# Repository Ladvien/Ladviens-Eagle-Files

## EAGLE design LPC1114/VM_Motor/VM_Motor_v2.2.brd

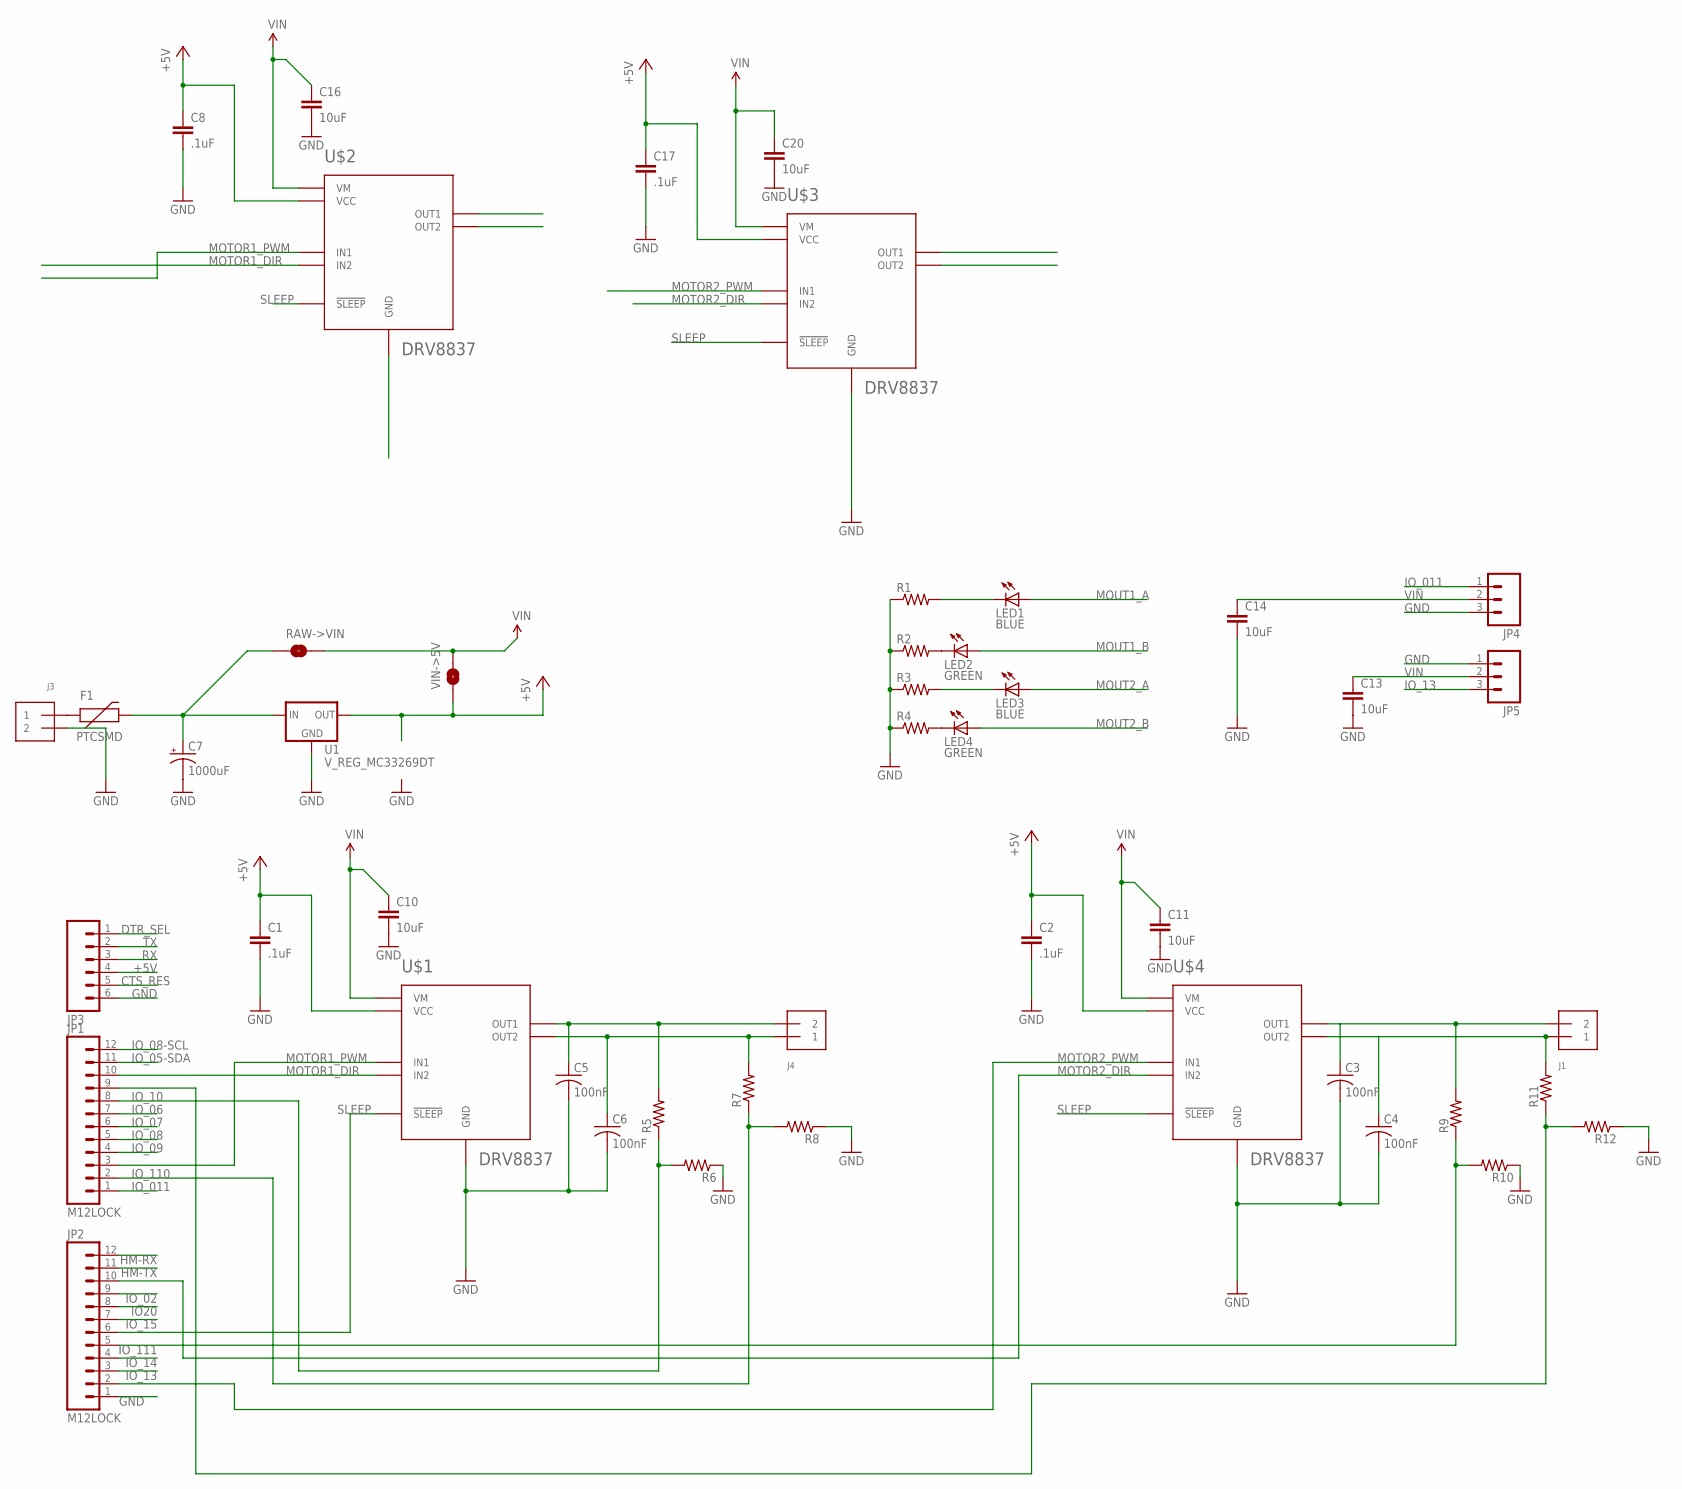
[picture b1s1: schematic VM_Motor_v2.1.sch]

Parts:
C1, C2, C8, C17: .1uF; 0402-CAP
C3, C4, C5, C6: 100nF; C0402
C7: 1000uF; 150CLZ-0810
C10, C11, C13, C14, C16, C20: 10uF; 0402-CAP
F1: PTCSMD; PTC-1206
J1, J3, J4: TERMBLOCK_1X2; TERMBLOCK_1X2-3.5MM
JP1, JP2: M12LOCK; 1X12_LOCK
JP3: M06LOCK; 1X06_LOCK
JP4, JP5: M03LOCK; 1X03_LOCK
LED1, LED3: BLUE; CHIP-LED0603
LED2, LED4: GREEN; CHIP-LED0603
R1, R2, R3, R4, R5, R6, R7, R8, R9, R10, R11, R12: R-US_R0402; R0402
RAW->VIN: SOLDERJUMPERNO; SJ_2S-NO
U1: V_REG_MC33269DT; DPAK
U$1, U$2, U$3, U$4: DRV8837; QFN8
VIN->5V: SOLDERJUMPERNO; SJ_2S-NO

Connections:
+5V: C1.1, C2.1, C8.1, C17.1, JP3.4, U1.4 (OUT), U$1.P$8 (VCC), U$2.P$8 (VCC), U$3.P$8 (VCC), U$4.P$8 (VCC), VIN->5V.1
CTS_RES: JP3.5
DTR_SEL: JP3.1
GND: C1.2, C2.2, C3.2, C4.2, C5.2, C6.2, C7.-, C8.2, C10.2, C11.2, C13.2, C14.2, C16.2, C17.2, C20.2, J3.2, JP2.1, JP3.6, JP4.3, JP5.1, R1.1, R2.1, R3.1, R4.1, R6.1, R8.1, R10.1, R12.1, U1.1 (GND), U$1.P$4 (GND), U$1.P$9 (GND), U$1.P$10 (GND), U$1.P$11 (GND), U$2.P$4 (GND), U$2.P$9 (GND), U$2.P$10 (GND), U$2.P$11 (GND), U$3.P$4 (GND), U$3.P$9 (GND), U$3.P$10 (GND), U$3.P$11 (GND), U$4.P$4 (GND), U$4.P$9 (GND), U$4.P$10 (GND), U$4.P$11 (GND)
HM-RX: JP2.12
HM-TX: JP2.11
IO20: JP2.8
IO_02: JP2.9
IO_05-SDA: JP1.11
IO_06: JP1.7
IO_07: JP1.6
IO_08: JP1.5
IO_08-SCL: JP1.12
IO_09: JP1.4
IO_10: JP1.8, R5.1, R6.2
IO_011: JP1.1, JP4.1
IO_11: JP1.9, R11.1, R12.2
IO_13: JP2.3, JP5.3
IO_14: JP2.4
IO_15: JP2.7
IO_110: JP1.2, R7.1, R8.2
IO_111: JP2.5, R9.1, R10.2
MOTOR1_DIR: JP1.10, U$1.P$5 (IN2), U$2.P$5 (IN2)
MOTOR1_PWM: JP1.3, U$1.P$6 (IN1), U$2.P$6 (IN1)
MOTOR2_DIR: JP2.10, U$3.P$5 (IN2), U$4.P$5 (IN2)
MOTOR2_PWM: JP2.2, U$3.P$6 (IN1), U$4.P$6 (IN1)
MOUT1_A: C5.1, J4.2, LED1.A, R5.2, U$1.P$2 (OUT1), U$2.P$2 (OUT1)
MOUT1_B: C6.1, J4.1, LED2.A, R7.2, U$1.P$3 (OUT2), U$2.P$3 (OUT2)
MOUT2_A: C3.1, J1.2, LED3.A, R9.2, U$3.P$2 (OUT1), U$4.P$2 (OUT1)
MOUT2_B: C4.1, J1.1, LED4.A, R11.2, U$3.P$3 (OUT2), U$4.P$3 (OUT2)
unnamed: LED2.C, R2.2
unnamed: LED4.C, R4.2
unnamed: LED1.C, R1.2
unnamed: LED3.C, R3.2
unnamed: F1.1, J3.1
RAW: C7.+, F1.2, RAW->VIN.1, U1.3 (IN)
RX: JP3.3
SLEEP: JP2.6, U$1.P$7 (!SLEEP), U$2.P$7 (!SLEEP), U$3.P$7 (!SLEEP), U$4.P$7 (!SLEEP)
TX: JP3.2
VIN: C10.1, C11.1, C13.1, C14.1, C16.1, C20.1, JP4.2, JP5.2, RAW->VIN.2, U$1.P$1 (VM), U$2.P$1 (VM), U$3.P$1 (VM), U$4.P$1 (VM), VIN->5V.2

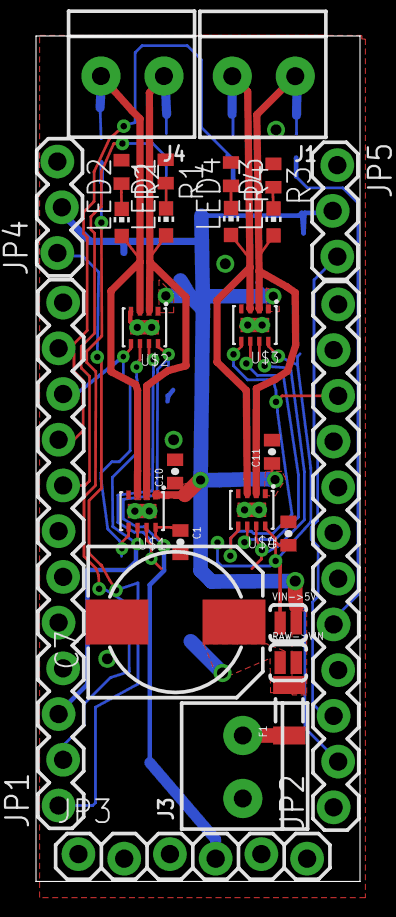
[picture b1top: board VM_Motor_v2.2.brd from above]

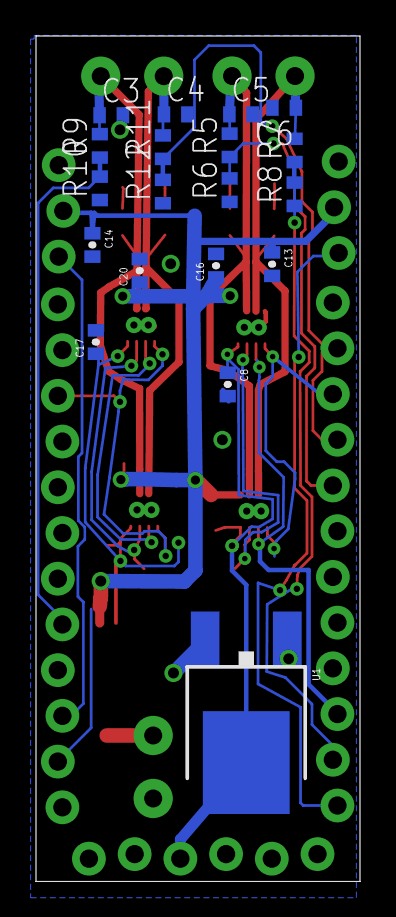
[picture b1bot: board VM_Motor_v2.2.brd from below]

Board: 2 copper layers, 18.0 x 47.0 mm, 47 parts (19 on the bottom side), 24 nets.

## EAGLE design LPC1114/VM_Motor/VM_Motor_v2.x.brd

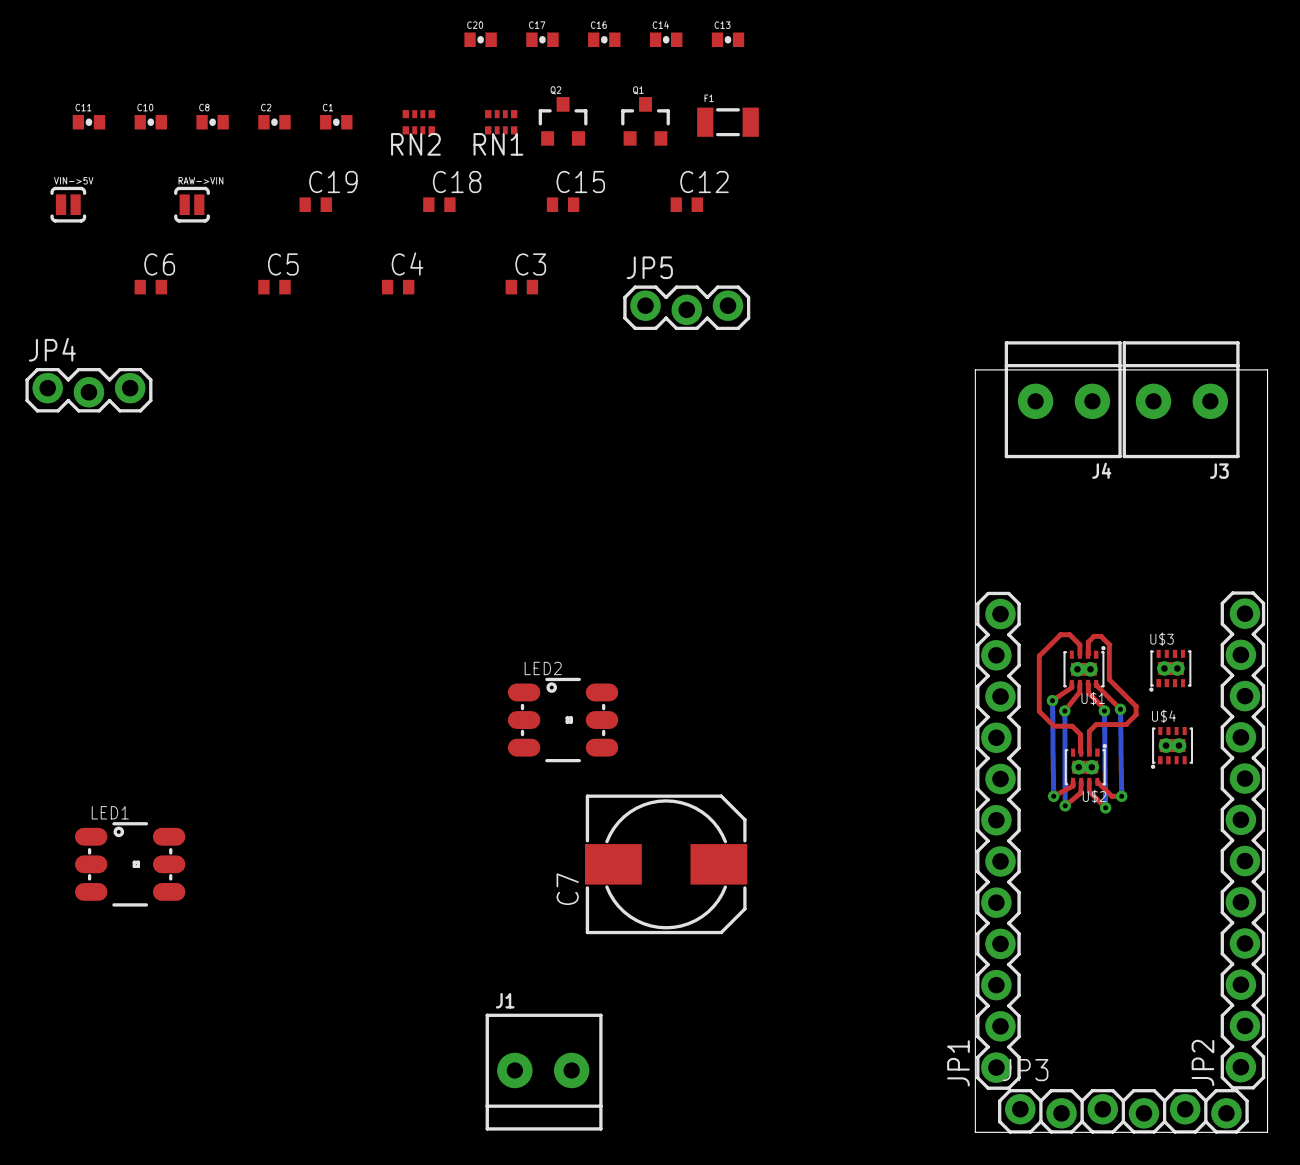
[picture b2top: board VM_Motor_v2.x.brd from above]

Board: 2 copper layers, 18.0 x 47.0 mm, 40 parts (0 on the bottom side), 28 nets.

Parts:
C1, C2, C8, C17: .1uF; 0402-CAP
C3, C4, C5, C6, C12, C15, C18, C19: 100nF; C0402
C7: 1000uF; 150CLZ-0810
C10, C11, C13, C14, C16, C20: 10uF; 0402-CAP
F1: PTCSMD; PTC-1206
J1, J3, J4: TERMBLOCK_1X2-3.5MM
JP1, JP2: M12LOCK; 1X12_LOCK
JP3: 1X06_LOCK
JP4, JP5: 1X03_LOCK
LED1, LED2: LED-TRICOLOR-5050NO_IC; LED-TRICOLOR-5050
Q1, Q2: MMBT2222A; SOT23-3
RAW->VIN: SOLDERJUMPERNO; SJ_2S-NO
RN1, RN2: 4X0402ARV341
U$1, U$2, U$3, U$4: DRV8837; QFN8
VIN->5V: SOLDERJUMPERNO; SJ_2S-NO

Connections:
+5V: C1.1, C2.1, C8.1, C17.1, JP3.4, U$1.P$8, U$2.P$8, U$3.P$8, U$4.P$8, VIN->5V.1
GND: C1.2, C2.2, C3.2, C4.2, C5.2, C6.2, C7.-, C8.2, C10.2, C11.2, C12.2, C13.2, C14.2, C15.2, C16.2, C17.2, C18.2, C19.2, C20.2, J3.2, JP2.1, JP3.6, JP4.3, JP5.1, Q1.2, Q2.2, RN1.1, RN1.4, RN2.1, RN2.4, U$1.P$4, U$1.P$9, U$1.P$10, U$1.P$11, U$2.P$4, U$2.P$9, U$2.P$10, U$2.P$11, U$3.P$4, U$3.P$9, U$3.P$10, U$3.P$11, U$4.P$4, U$4.P$9, U$4.P$10, U$4.P$11
IO20: JP2.8, RN2.3
IO_07: JP1.6, RN1.3
IO_011: JP1.1, JP4.1
IO_13: JP2.3, JP5.3
MOTOR1_DIR: JP1.10, U$1.P$5, U$2.P$5
MOTOR1_PWM: JP1.9, U$1.P$6, U$2.P$6
MOTOR2_DIR: JP2.10, U$3.P$5, U$4.P$5
MOTOR2_PWM: JP2.2, U$3.P$6, U$4.P$6
MOUT1_A: C5.1, C12.1, J4.2, LED1.3, U$1.P$2, U$2.P$2
MOUT1_B: C6.1, C15.1, J4.1, LED1.1, U$1.P$3, U$2.P$3
MOUT2_A: C3.1, C18.1, J1.2, LED2.3, U$3.P$2, U$4.P$2
MOUT2_B: C4.1, C19.1, J1.1, LED2.1, U$3.P$3, U$4.P$3
unnamed: Q1.1, RN2.6
unnamed: LED1.4, RN1.8
unnamed: LED1.6, RN1.5
unnamed: LED2.4, RN2.8
unnamed: LED1.5, RN1.7
unnamed: Q1.3, RN2.2
unnamed: Q2.3, RN1.2
unnamed: Q2.1, RN1.6
unnamed: LED2.6, RN2.5
unnamed: LED2.5, RN2.7
unnamed: F1.1, J3.1
RAW: C7.+, F1.2, RAW->VIN.1
SLEEP: JP2.6, U$1.P$7, U$2.P$7, U$3.P$7, U$4.P$7
VIN: C10.1, C11.1, C13.1, C14.1, C16.1, JP4.2, JP5.2, LED1.2, LED2.2, RAW->VIN.2, U$1.P$1, U$2.P$1, U$3.P$1, U$4.P$1, VIN->5V.2

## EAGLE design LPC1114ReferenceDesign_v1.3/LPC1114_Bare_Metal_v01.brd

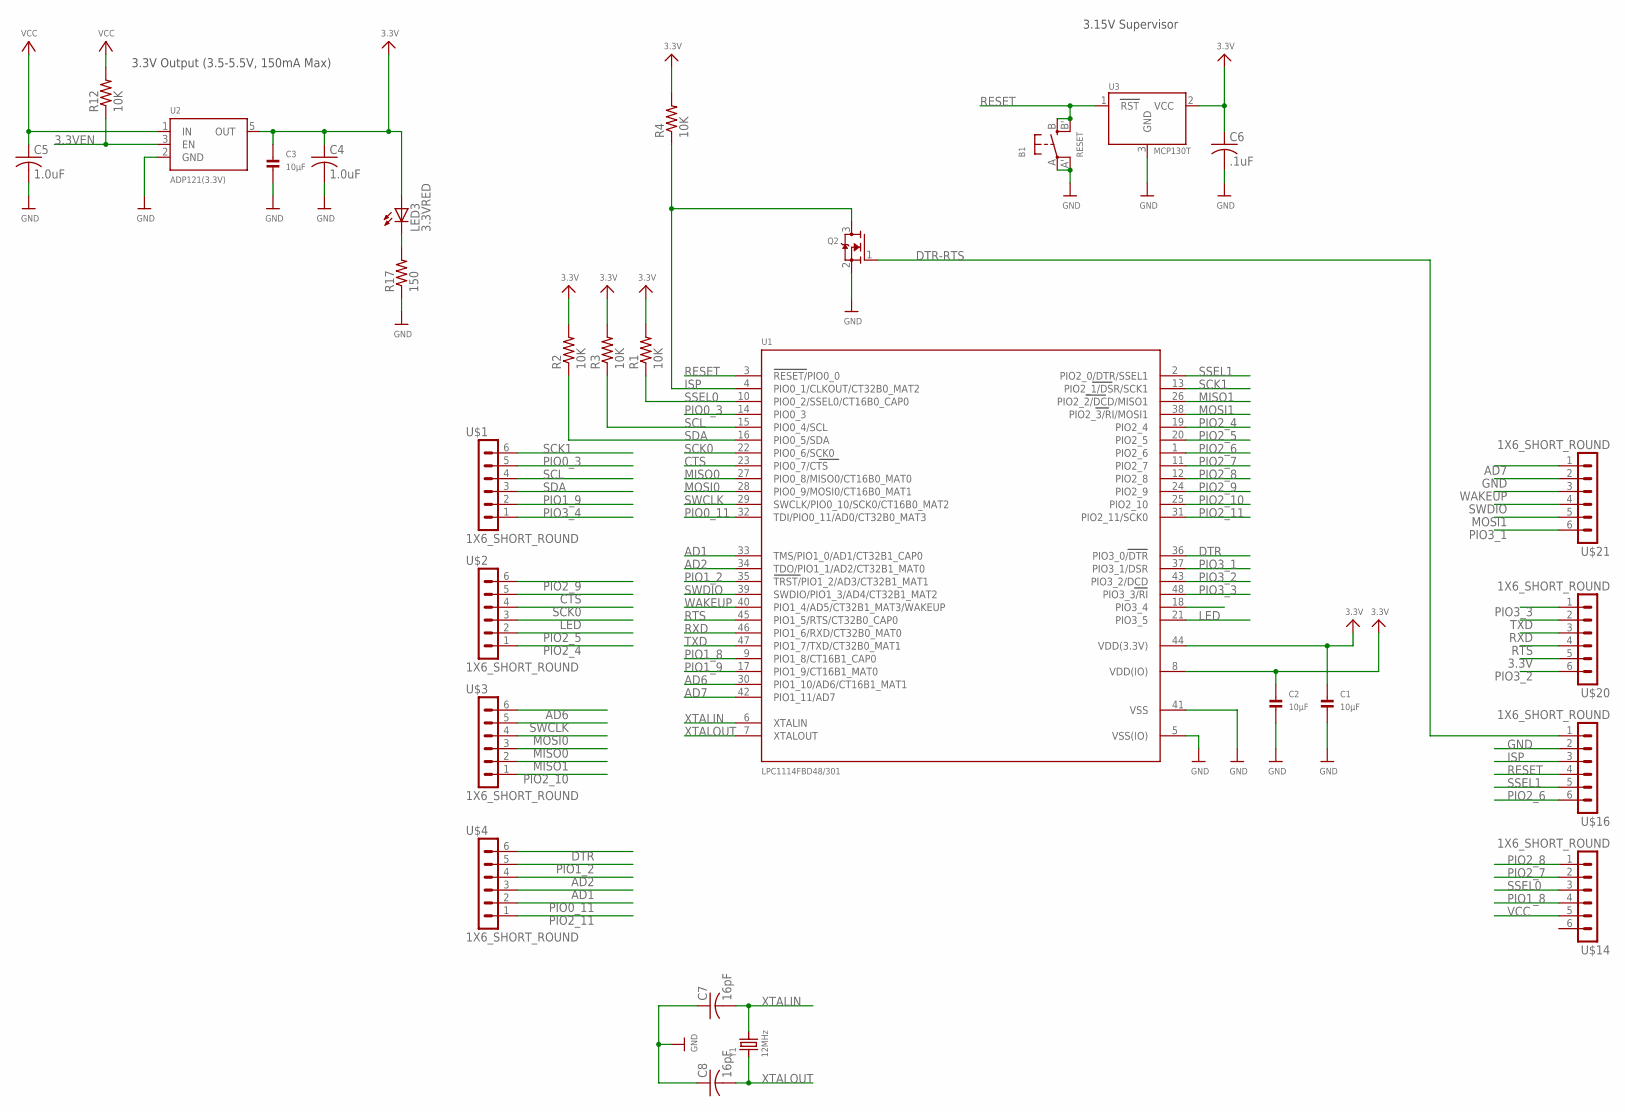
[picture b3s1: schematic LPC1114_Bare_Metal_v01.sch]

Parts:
B1: RESET; EVQ-Q2
C1, C2, C3: 10µF; 0805
C4, C5: 1.0uF; C0402K
C6: .1uF; C0402K
C7, C8: 16pF; C0402K
LED3: 3.3VRED; SML0603
Q2: MOSFET-NREFLOW; SOT23
R1, R2, R3, R4, R12: 10K; R0402
R17: 150; R0402
U1: LPC1114FBD48/301; LQFP48
U2: ADP121(3.3V); SOT23-5
U3: MCP130T; SOT23-R
U$1, U$2, U$3, U$4, U$14, U$16, U$20, U$21: 1X6_SHORT_ROUND
Y1: 12MHz; CRYSTAL_3.2X2.5

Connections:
3.3V: C1.1, C2.1, C3.1, C4.1, C6.1, LED3.A, R1.2, R2.2, R3.2, R4.2, U1.8 (VDD(IO)), U1.44 (VDD(3.3V)), U2.5 (OUT), U3.2 (VCC), U$20.5
3.3VEN: R12.1, U2.3 (EN)
AD1: U1.33 (TMS/PIO1_0/AD1/CT32B1_CAP0), U$4.3
AD2: U1.34 (TDO/PIO1_1/AD2/CT32B1_MAT0), U$4.4
AD6: U1.30 (PIO1_10/AD6/CT16B1_MAT1), U$3.6
AD7: U1.42 (PIO1_11/AD7), U$21.1
CTS: U1.23 (PIO0_7/CTS), U$2.5
DTR: U1.36 (PIO3_0/DTR), U$4.6
DTR-RTS: Q2.1 (G), U$16.1
GND: B1.A, B1.A' (P1), C1.2, C2.2, C3.2, C4.2, C5.2, C6.2, C7.1, C8.1, Q2.2 (S), R17.1, U1.5 (VSS(IO)), U1.41 (VSS), U2.2 (GND), U3.3 (GND), U$16.2, U$21.2
ISP: Q2.3 (D), R4.1, U1.4 (PIO0_1/CLKOUT/CT32B0_MAT2), U$16.3
LED: U1.21 (PIO3_5), U$2.3
MISO0: U1.27 (PIO0_8/MISO0/CT16B0_MAT0), U$3.3
MISO1: U1.26 (PIO2_2/DCD/MISO1), U$3.2
MOSI0: U1.28 (PIO0_9/MOSI0/CT16B0_MAT1), U$3.4
MOSI1: U1.38 (PIO2_3/RI/MOSI1), U$21.5
unnamed: LED3.C, R17.2
PIO0_3: U1.14 (PIO0_3), U$1.5
PIO0_11: U1.32 (TDI/PIO0_11/AD0/CT32B0_MAT3), U$4.2
PIO1_2: U1.35 (TRST/PIO1_2/AD3/CT32B1_MAT1), U$4.5
PIO1_8: U1.9 (PIO1_8/CT16B1_CAP0), U$14.4
PIO1_9: U1.17 (PIO1_9/CT16B1_MAT0), U$1.2
PIO2_4: U1.19 (PIO2_4), U$2.1
PIO2_5: U1.20 (PIO2_5), U$2.2
PIO2_6: U1.1 (PIO2_6), U$16.6
PIO2_7: U1.11 (PIO2_7), U$14.2
PIO2_8: U1.12 (PIO2_8), U$14.1
PIO2_9: U1.24 (PIO2_9), U$2.6
PIO2_10: U1.25 (PIO2_10), U$3.1
PIO2_11: U1.31 (PIO2_11/SCK0), U$4.1
PIO3_1: U1.37 (PIO3_1/DSR), U$21.6
PIO3_2: U1.43 (PIO3_2/DCD), U$20.6
PIO3_3: U1.48 (PIO3_3/RI), U$20.1
PIO3_4: U1.18 (PIO3_4), U$1.1
RESET: B1.B (S), B1.B' (S1), U1.3 (RESET/PIO0_0), U3.1 (RST), U$16.4
RTS: U1.45 (PIO1_5/RTS/CT32B0_CAP0), U$20.4
RXD: U1.46 (PIO1_6/RXD/CT32B0_MAT0), U$20.3
SCK0: U1.22 (PIO0_6/SCK0), U$2.4
SCK1: U1.13 (PIO2_1/DSR/SCK1), U$1.6
SCL: R3.1, U1.15 (PIO0_4/SCL), U$1.4
SDA: R2.1, U1.16 (PIO0_5/SDA), U$1.3
SSEL0: R1.1, U1.10 (PIO0_2/SSEL0/CT16B0_CAP0), U$14.3
SSEL1: U1.2 (PIO2_0/DTR/SSEL1), U$16.5
SWCLK: U1.29 (SWCLK/PIO0_10/SCK0/CT16B0_MAT2), U$3.5
SWDIO: U1.39 (SWDIO/PIO1_3/AD4/CT32B1_MAT2), U$21.4
TXD: U1.47 (PIO1_7/TXD/CT32B0_MAT1), U$20.2
VCC: C5.1, R12.2, U2.1 (IN), U$14.5
WAKEUP: U1.40 (PIO1_4/AD5/CT32B1_MAT3/WAKEUP), U$21.3
XTALIN: C7.2, U1.6 (XTALIN), Y1.2
XTALOUT: C8.2, U1.7 (XTALOUT), Y1.1

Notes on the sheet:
3.3V Output (3.5-5.5V, 150mA Max)
3.15V Supervisor

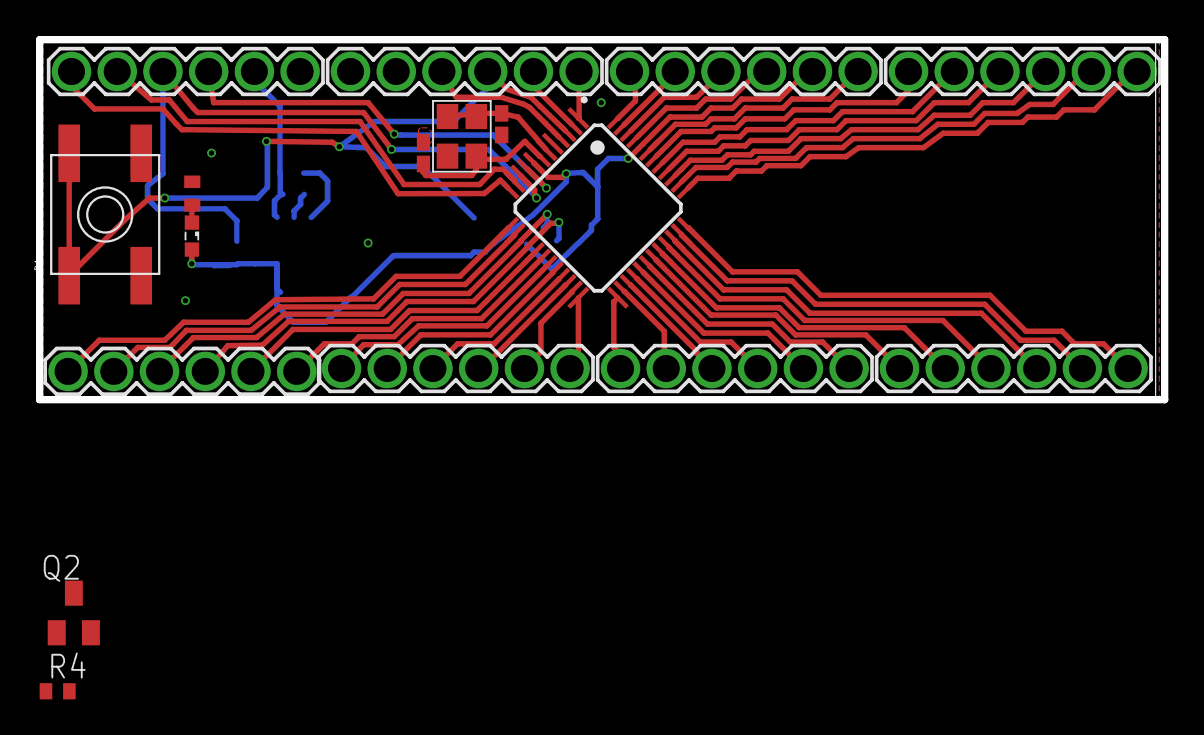
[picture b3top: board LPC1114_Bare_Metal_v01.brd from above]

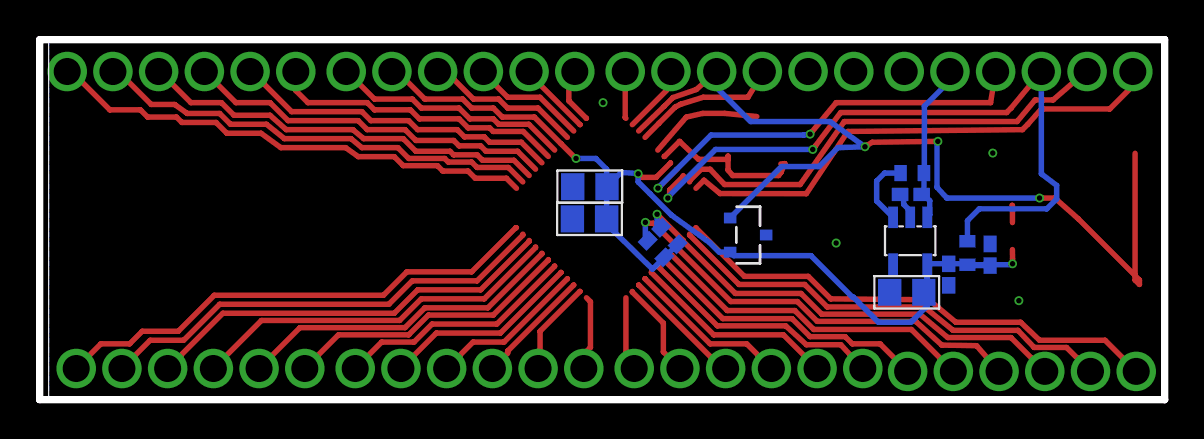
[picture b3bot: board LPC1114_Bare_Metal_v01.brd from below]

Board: 2 copper layers, 62.5 x 20.0 mm, 29 parts (12 on the bottom side), 50 nets.

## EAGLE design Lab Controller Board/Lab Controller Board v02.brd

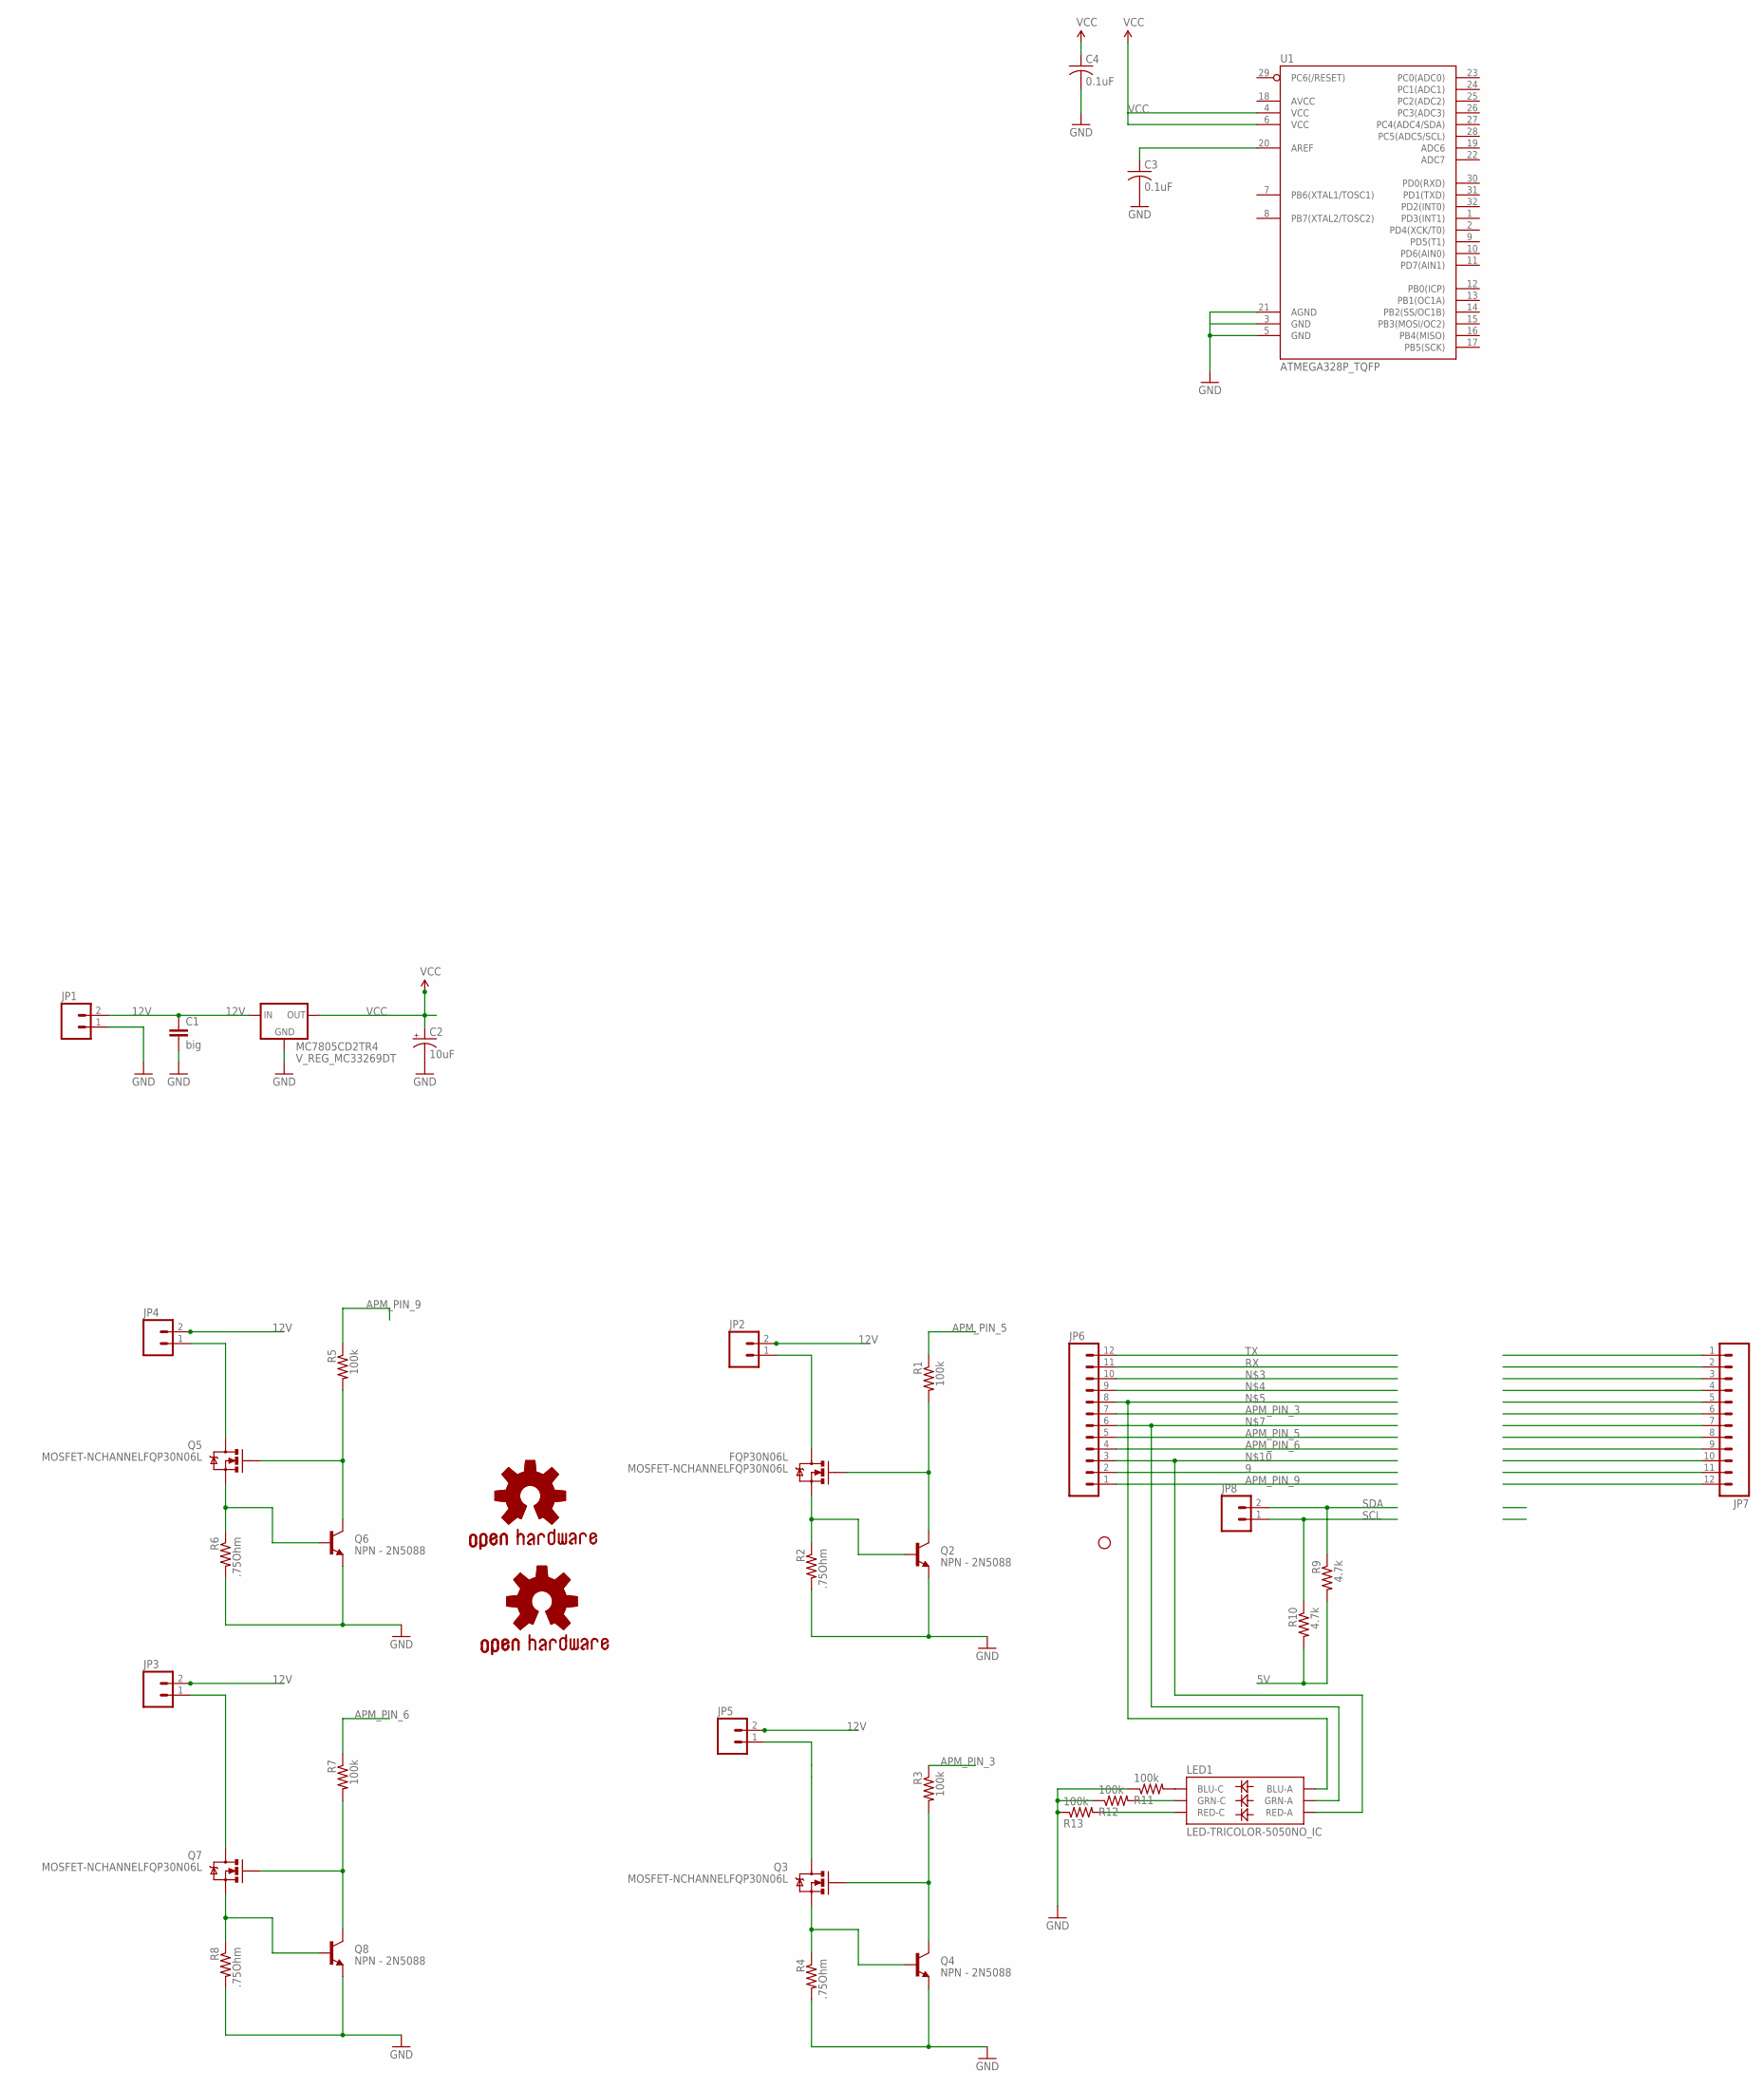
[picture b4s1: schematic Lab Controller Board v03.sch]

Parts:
C1: big; CAP-PTH-5MM
C2: 10uF; EIA3528
C3, C4: 0.1uF; C0402
FQP30N06L: MOSFET-NCHANNELFQP30N06L; TO220V
GOLD_ORB_SM1: OSHWLOGO_GOLD_ORB_MED; OSHW1
GOLD_ORB_SM2: OSHWLOGO_GOLD_ORB_SM; OSHW2
JP1, JP2, JP3, JP4, JP5: M025MM; SCREWTERMINAL-5MM-2
JP6, JP7: M12PTH; 1X12
JP8: M02LOCK; 1X02_LOCK
LED1: LED-TRICOLOR-5050NO_IC; LED-TRICOLOR-5050
MC7805CD2TR4: V_REG_MC33269DT; DPAK
Q2, Q4, Q6, Q8: NPN - 2N5088; TO-92
Q3, Q5, Q7: MOSFET-NCHANNELFQP30N06L; TO220V
R1, R3, R5, R7, R11, R12, R13: 100k; R0805W
R2, R4, R6, R8: .75Ohm; 0411V
R9, R10: 4.7k; M0805
STANDOFF1: STAND-OFF
U1: ATMEGA328P_TQFP; TQFP32-08

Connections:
12V: C1.1, JP1.2, JP2.2, JP3.2, JP4.2, JP5.2, MC7805CD2TR4.3 (IN)
APM_PIN_3: JP6.7, R3.1; also elsewhere on the board
APM_PIN_5: JP6.5, R1.1; also elsewhere on the board
APM_PIN_6: JP6.4, R7.1; also elsewhere on the board
APM_PIN_9: JP6.1, R5.1; also elsewhere on the board
FET_SOURCE: FQP30N06L.3 (S), Q2.2 (B), R2.1
FET_SOURCE1: Q3.3 (S), Q4.2 (B), R4.1
FET_SOURCE2: Q5.3 (S), Q6.2 (B), R6.1
FET_SOURCE3: Q7.3 (S), Q8.2 (B), R8.1
GND: C1.2, C2.C (-), C3.2, C4.2, JP1.1, MC7805CD2TR4.1 (GND), Q2.1 (E), Q4.1 (E), Q6.1 (E), Q8.1 (E), R2.2, R4.2, R6.2, R8.2, R11.1, R12.1, R13.1, U1.3 (GND), U1.5 (GND), U1.21 (AGND); also elsewhere on the board
LED_DRAIN: FQP30N06L.2 (D), JP2.1
LED_DRAIN1: JP5.1, Q3.2 (D)
LED_DRAIN2: JP4.1, Q5.2 (D)
LED_DRAIN3: JP3.1, Q7.2 (D)
unnamed 14: JP6.10; also elsewhere on the board
unnamed 15: JP6.9; also elsewhere on the board
unnamed 16: JP6.8, LED1.3 (BLU-A); also elsewhere on the board
unnamed: LED1.4 (BLU-C), R11.2
unnamed 18: JP6.6, LED1.1 (GRN-A); also elsewhere on the board
unnamed: LED1.6 (GRN-C), R12.2
unnamed: LED1.5 (RED-C), R13.2
unnamed 21: JP6.3, LED1.2 (RED-A); also elsewhere on the board
unnamed 22: JP7.1; also elsewhere on the board
unnamed 23: JP7.2; also elsewhere on the board
unnamed 24: JP7.3; also elsewhere on the board
unnamed 25: JP7.4; also elsewhere on the board
unnamed 26: JP7.5; also elsewhere on the board
unnamed 27: JP7.6; also elsewhere on the board
unnamed 28: JP7.7; also elsewhere on the board
unnamed 29: JP7.8; also elsewhere on the board
unnamed 30: JP7.9; also elsewhere on the board
unnamed 31: JP7.10; also elsewhere on the board
unnamed 32: JP7.11; also elsewhere on the board
unnamed 33: JP7.12; also elsewhere on the board
unnamed: C3.1, U1.20 (AREF)
PWM_B: FQP30N06L.1 (G), Q2.3 (C), R1.2
PWM_B1: Q3.1 (G), Q4.3 (C), R3.2
PWM_B2: Q5.1 (G), Q6.3 (C), R5.2
PWM_B3: Q7.1 (G), Q8.3 (C), R7.2
RX: JP6.11; also elsewhere on the board
SCL: JP8.1, R10.1; also elsewhere on the board
SDA: JP8.2, R9.1; also elsewhere on the board
TX: JP6.12; also elsewhere on the board

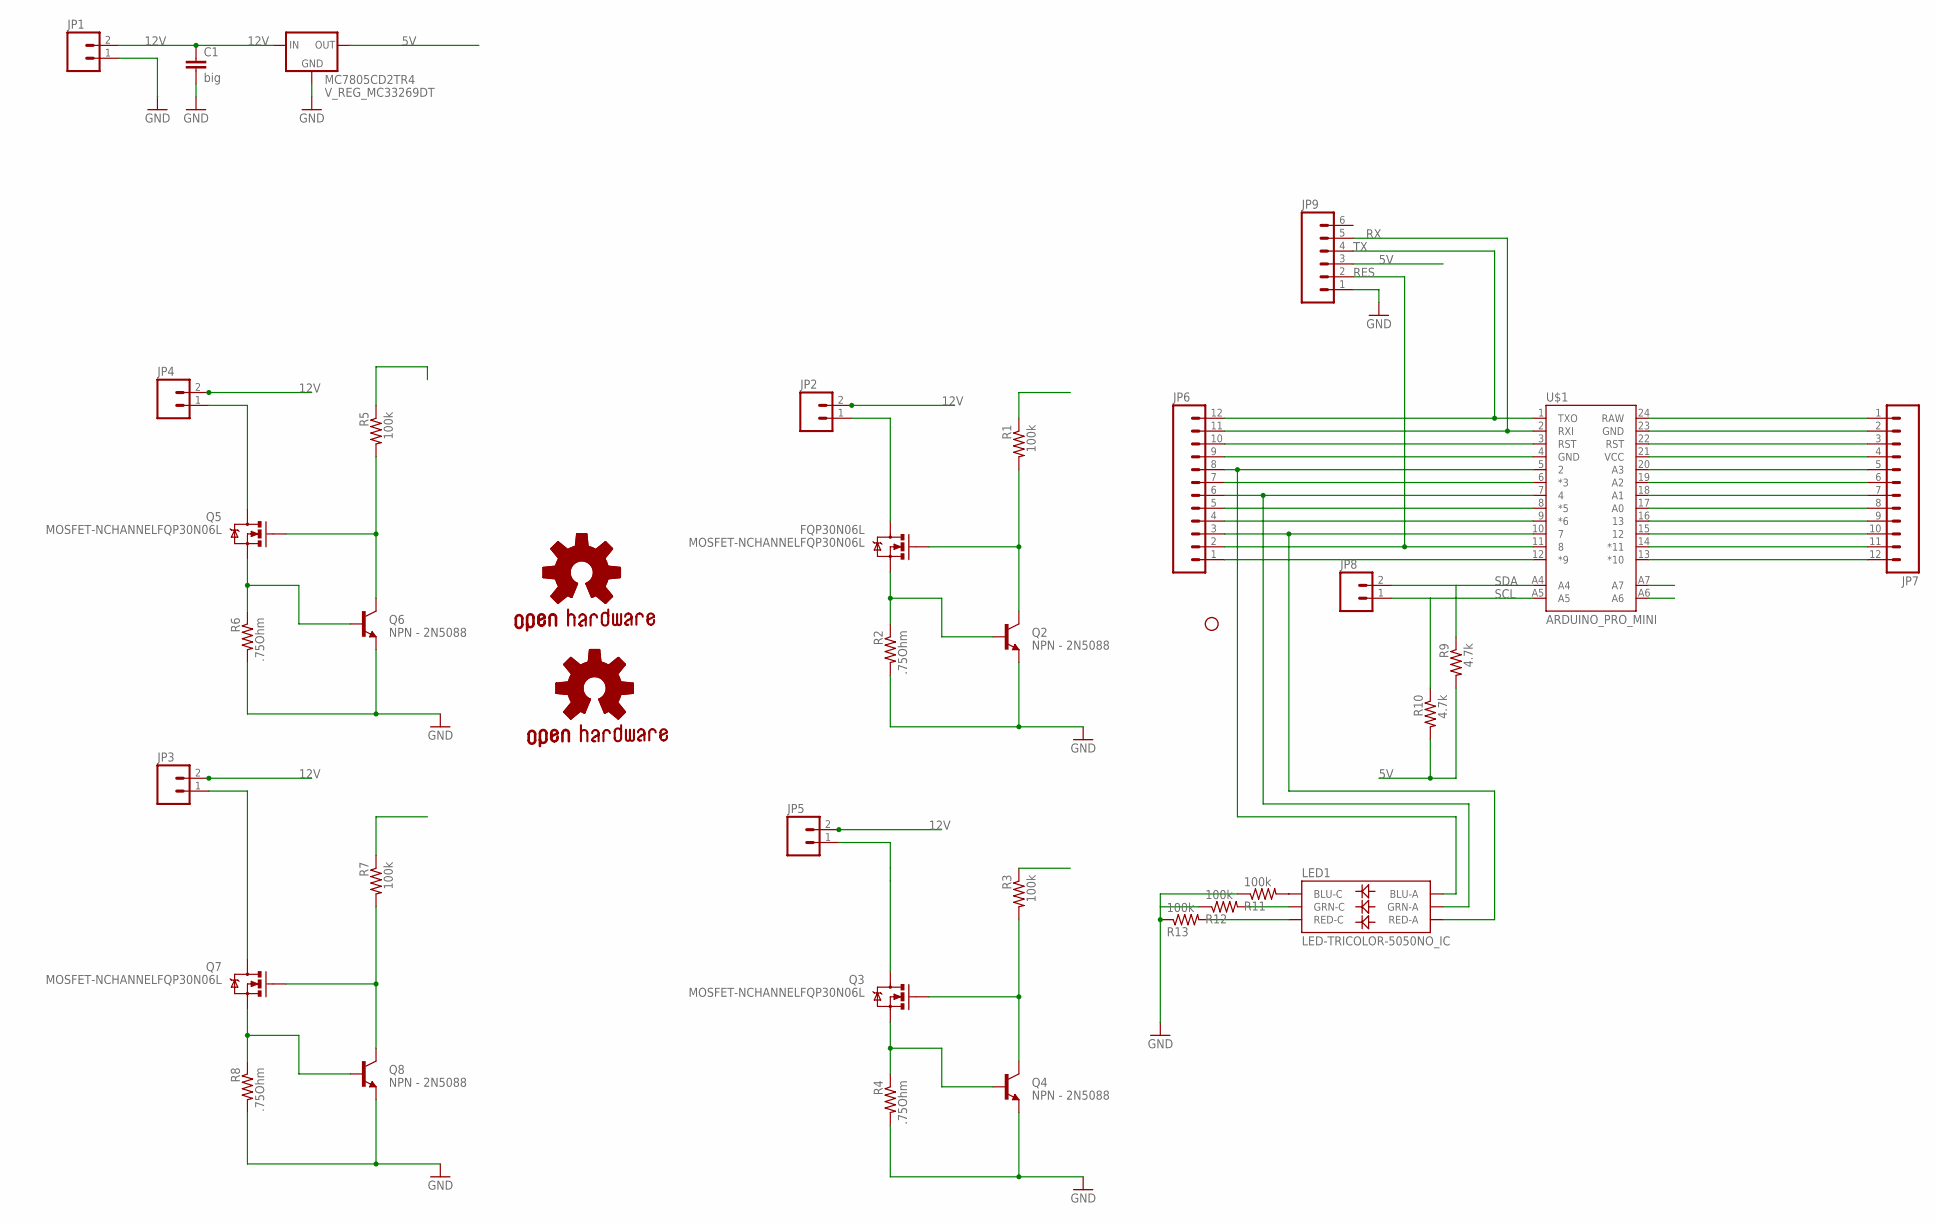
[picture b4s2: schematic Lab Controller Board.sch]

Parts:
C1: big; CAP-PTH-5MM
FQP30N06L: MOSFET-NCHANNELFQP30N06L; TO220V
GOLD_ORB_SM1: OSHWLOGO_GOLD_ORB_MED; OSHW1
GOLD_ORB_SM2: OSHWLOGO_GOLD_ORB_SM; OSHW2
JP1, JP2, JP3, JP4, JP5: M025MM; SCREWTERMINAL-5MM-2
JP6, JP7: M12PTH; 1X12
JP8: M02LOCK; 1X02_LOCK
JP9: M06LOCK; 1X06_LOCK
LED1: LED-TRICOLOR-5050NO_IC; LED-TRICOLOR-5050
MC7805CD2TR4: V_REG_MC33269DT; DPAK
Q2, Q4, Q6, Q8: NPN - 2N5088; TO-92
Q3, Q5, Q7: MOSFET-NCHANNELFQP30N06L; TO220V
R1, R3, R5, R7, R11, R12, R13: 100k; R0805W
R2, R4, R6, R8: .75Ohm; 0411V
R9, R10: 4.7k; M0805
STANDOFF1: STAND-OFF
U$1: ARDUINO_PRO_MINI

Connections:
12V: C1.1, JP1.2, JP2.2, JP3.2, JP4.2, JP5.2, MC7805CD2TR4.3 (IN)
APM_PIN_3: JP6.7, R3.1, U$1.6 (*3)
APM_PIN_5: JP6.5, R1.1, U$1.8 (*5)
APM_PIN_6: JP6.4, R7.1, U$1.9 (*6)
APM_PIN_9: JP6.1, R5.1, U$1.12 (*9)
FET_SOURCE: FQP30N06L.3 (S), Q2.2 (B), R2.1
FET_SOURCE1: Q3.3 (S), Q4.2 (B), R4.1
FET_SOURCE2: Q5.3 (S), Q6.2 (B), R6.1
FET_SOURCE3: Q7.3 (S), Q8.2 (B), R8.1
GND: C1.2, JP1.1, JP9.1, MC7805CD2TR4.1 (GND), Q2.1 (E), Q4.1 (E), Q6.1 (E), Q8.1 (E), R2.2, R4.2, R6.2, R8.2, R11.1, R12.1, R13.1; also elsewhere on the board
LED_DRAIN: FQP30N06L.2 (D), JP2.1
LED_DRAIN1: JP5.1, Q3.2 (D)
LED_DRAIN2: JP4.1, Q5.2 (D)
LED_DRAIN3: JP3.1, Q7.2 (D)
unnamed: JP6.10, U$1.3 (RST)
unnamed: JP6.9, U$1.4 (GND)
unnamed: JP6.8, LED1.3 (BLU-A), U$1.5 (2)
unnamed: LED1.4 (BLU-C), R11.2
unnamed: JP6.6, LED1.1 (GRN-A), U$1.7 (4)
unnamed: LED1.6 (GRN-C), R12.2
unnamed: LED1.5 (RED-C), R13.2
unnamed: JP6.3, LED1.2 (RED-A), U$1.10 (7)
unnamed: JP7.1, U$1.24 (RAW)
unnamed: JP7.2, U$1.23 (GND)
unnamed: JP7.3, U$1.22 (RST)
unnamed: JP7.4, U$1.21 (VCC)
unnamed: JP7.5, U$1.20 (A3)
unnamed: JP7.6, U$1.19 (A2)
unnamed: JP7.7, U$1.18 (A1)
unnamed: JP7.8, U$1.17 (A0)
unnamed: JP7.9, U$1.16 (13)
unnamed: JP7.10, U$1.15 (12)
unnamed: JP7.11, U$1.14 (*11)
unnamed: JP7.12, U$1.13 (*10)
PWM_B: FQP30N06L.1 (G), Q2.3 (C), R1.2
PWM_B1: Q3.1 (G), Q4.3 (C), R3.2
PWM_B2: Q5.1 (G), Q6.3 (C), R5.2
PWM_B3: Q7.1 (G), Q8.3 (C), R7.2
RX: JP6.11, JP9.5, U$1.2 (RXI)
SCL: JP8.1, R10.1, U$1.A5
SDA: JP8.2, R9.1, U$1.A4
TX: JP6.12, JP9.4, U$1.1 (TXO)

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

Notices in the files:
parts and their libraries:
SparkFun-Connectors: Licensing: Creative Commons ShareAlike 4.0 International - https://creativecommons.org/licenses/by-sa/4.0
microbuilder: This work is placed in the public domain, and may be freely used for commercial and non-commercial work with the following conditions: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
